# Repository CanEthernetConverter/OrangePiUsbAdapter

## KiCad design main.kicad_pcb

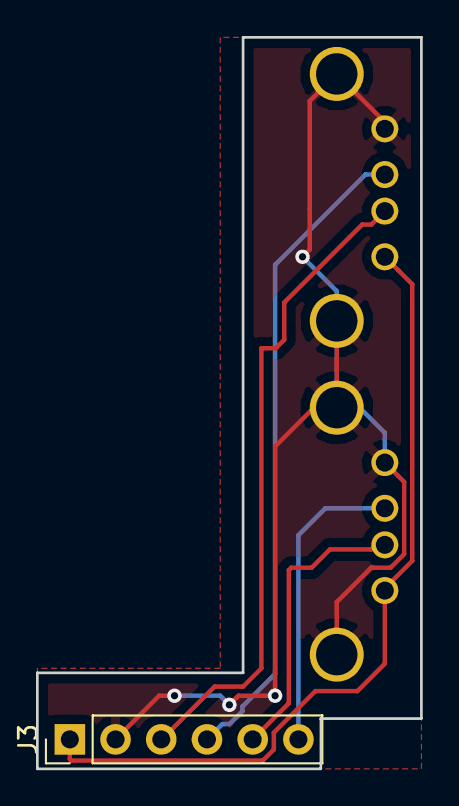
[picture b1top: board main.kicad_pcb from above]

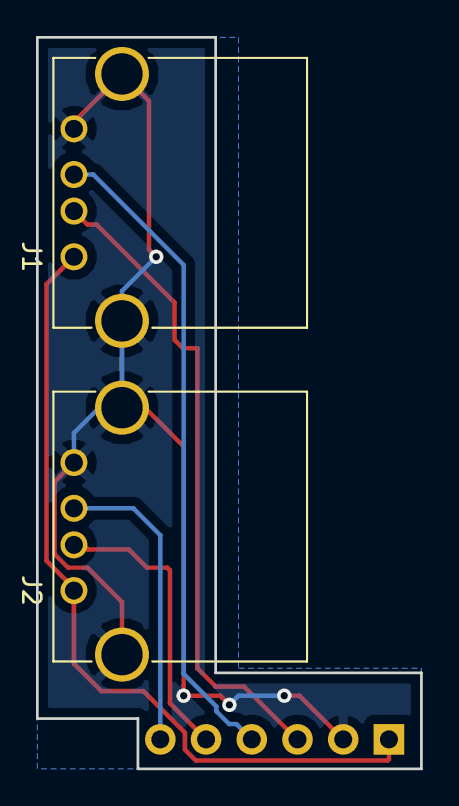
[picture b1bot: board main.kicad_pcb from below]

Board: 2 copper layers, 21.3 x 40.6 mm, 3 parts (2 on the bottom side), 6 nets.

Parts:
J1, J2: USB_A; UCCB_outline
J3: OrangePiCon; Pin_Header_Straight_1x06_Pitch2.54mm

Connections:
+5V: J1.1, J2.1, J3.1
GND: J1.4, J1.5, J2.4, J2.5, J3.2
USB1_DM: J1.2, J3.3
USB1_DP: J1.3, J3.4
USB2_DM: J2.2, J3.5
USB2_DP: J2.3, J3.6

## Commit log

2018-12-18 Init
2018-12-19 outline update
